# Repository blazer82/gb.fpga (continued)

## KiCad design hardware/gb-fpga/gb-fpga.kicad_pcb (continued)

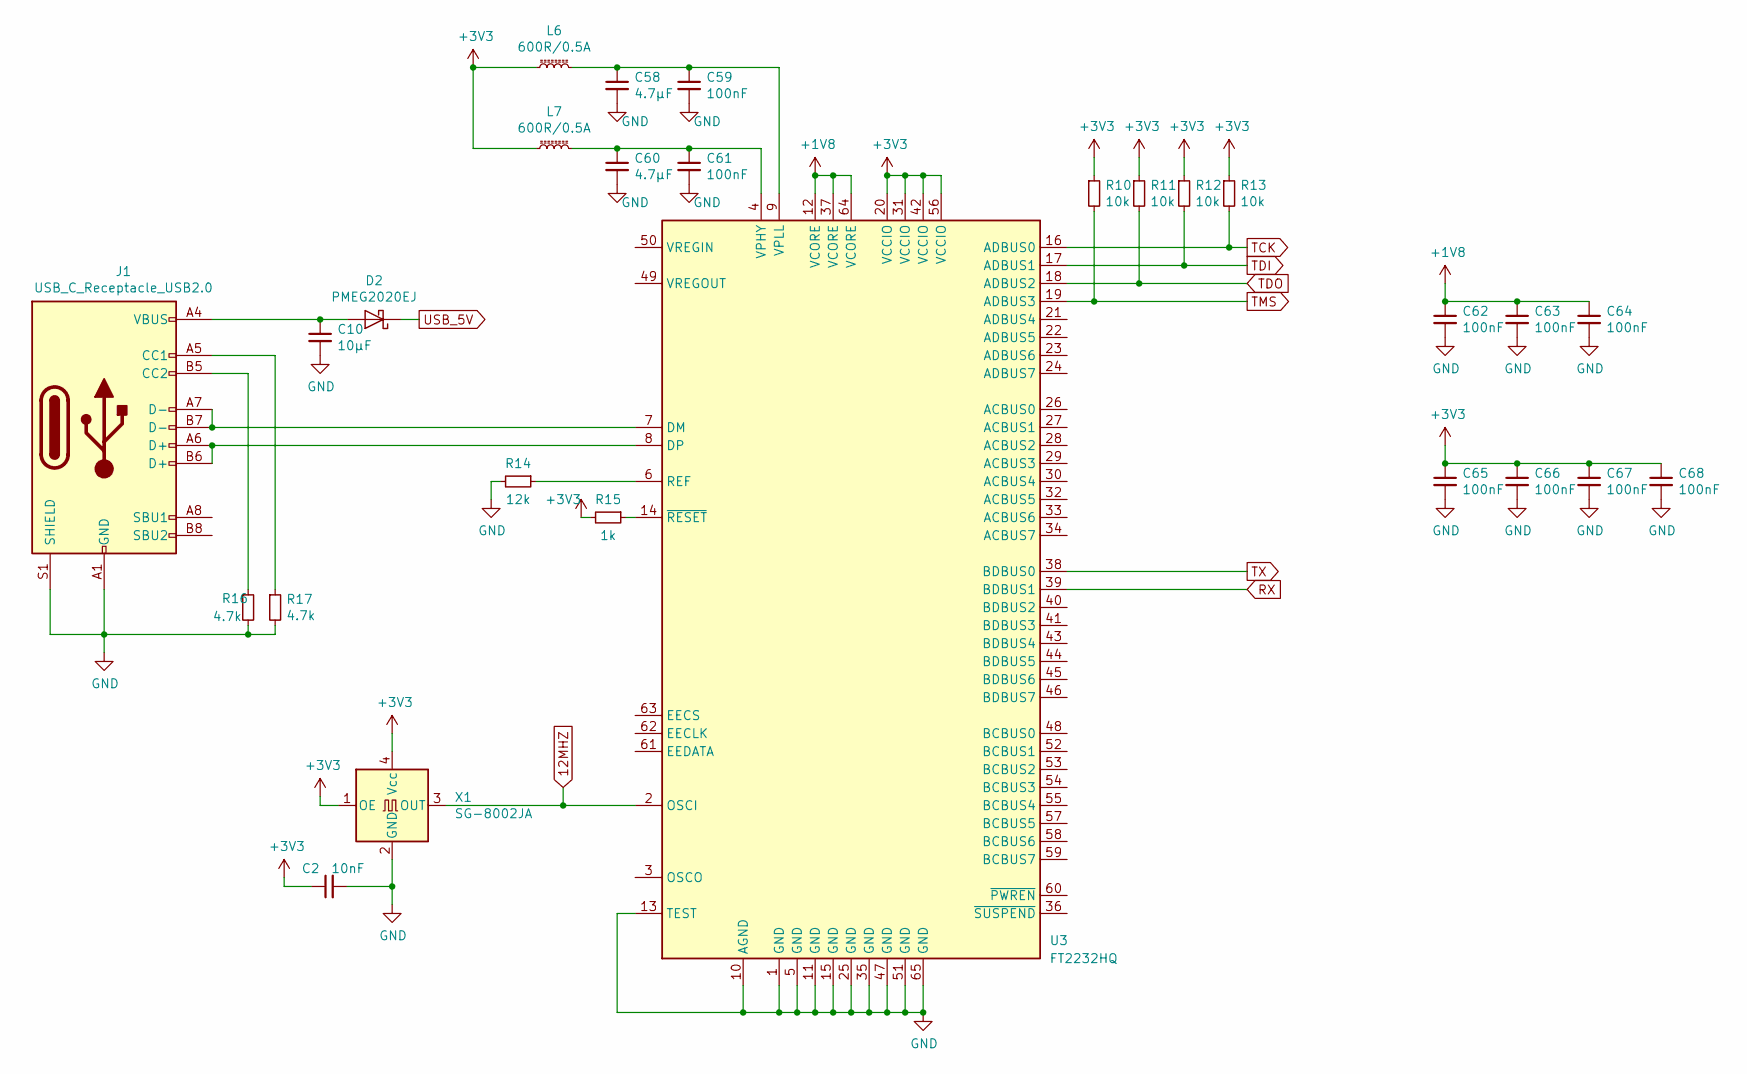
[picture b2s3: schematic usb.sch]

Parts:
C2: 10nF; C_0402_1005Metric; Manufacturer Part Number CL05B103KB5NNNC
C10: 10µF; C_0402_1005Metric; Manufacturer Part Number CL05A106MP5NUNC
C58, C60: 4.7µF; C_0402_1005Metric; Manufacturer Part Number CL05A475KP5NRNC
C59, C61, C62, C63, C64, C65, C66, C67, C68: 100nF; C_0402_1005Metric; Manufacturer Part Number CL05B104KO5NNNC
D2: PMEG2020EJ; D_SOD-323F; Manufacturer Part Number PMEG2020EJF
J1: USB_C_Receptacle_USB2.0; USB_C_Receptacle_XKB_U262-16XN-4BVC11; Manufacturer Part Number U262-161N-4BVC11
L6, L7: 600R/0.5A; L_0402_1005Metric; Manufacturer Part Number BLM15AX601SN1D
R10, R11, R12, R13: 10k; R_0402_1005Metric; Manufacturer Part Number RC0402JR-0710KL
R14: 12k; R_0402_1005Metric; Manufacturer Part Number RC0402FR-0712KL
R15: 1k; R_0402_1005Metric; Manufacturer Part Number RC0402JR-071KL
R16, R17: 4.7k; R_0402_1005Metric; Manufacturer Part Number RC0402JR-074K7L
U3: FT2232HQ; QFN-64-1EP_9x9mm_P0.5mm_EP4.35x4.35mm; Manufacturer Part Number FT2232HQ-REEL
X1: SG-8002JA; Oscillator_SMD_Abracon_ASE-4Pin_3.2x2.5mm; Manufacturer Part Number CB3LV-3C-12M000000

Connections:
12MHZ: U3.2 (OSCI), X1.3 (OUT); also elsewhere on the board
+1V8: C62.1, C63.1, C64.1, U3.12 (VCORE), U3.37 (VCORE), U3.64 (VCORE); also elsewhere on the board
+3V3: C2.1, C65.1, C66.1, C67.1, C68.1, L6.1, L7.1, R10.1, R11.1, R12.1, R13.1, R15.2, U3.20 (VCCIO), U3.31 (VCCIO), U3.42 (VCCIO), U3.56 (VCCIO), X1.1 (OE), X1.4 (Vcc); also elsewhere on the board
GND: C2.2, C10.2, C58.2, C59.2, C60.2, C61.2, C62.2, C63.2, C64.2, C65.2, C66.2, C67.2, C68.2, J1.A1 (GND), J1.A12 (GND), J1.B1 (GND), J1.B12 (GND), J1.S1 (SHIELD), R14.2, R16.2, R17.2, U3.1 (GND), U3.5 (GND), U3.10 (AGND), U3.11 (GND), U3.13 (TEST), U3.15 (GND), U3.25 (GND), U3.35 (GND), U3.47 (GND), U3.51 (GND), U3.65 (GND), X1.2 (GND); also elsewhere on the board
unnamed: C10.1, D2.2 (A), J1.A4 (VBUS), J1.A9 (VBUS), J1.B4 (VBUS), J1.B9 (VBUS)
unnamed: C58.1, C59.1, L6.2, U3.9 (VPLL)
unnamed: C60.1, C61.1, L7.2, U3.4 (VPHY)
unnamed: J1.A5 (CC1), R17.1
unnamed: J1.A6 (D+), J1.B6 (D+), U3.8 (DP)
unnamed: J1.A7 (D-), J1.B7 (D-), U3.7 (DM)
unnamed: J1.B5 (CC2), R16.1
unnamed: R14.1, U3.6 (REF)
unnamed: R15.1, U3.14 (~RESET)
RX: U3.39 (BDBUS1); also elsewhere on the board
TCK: R13.2, U3.16 (ADBUS0); also elsewhere on the board
TDI: R12.2, U3.17 (ADBUS1); also elsewhere on the board
TDO: R11.2, U3.18 (ADBUS2); also elsewhere on the board
TMS: R10.2, U3.19 (ADBUS3); also elsewhere on the board
TX: U3.38 (BDBUS0); also elsewhere on the board

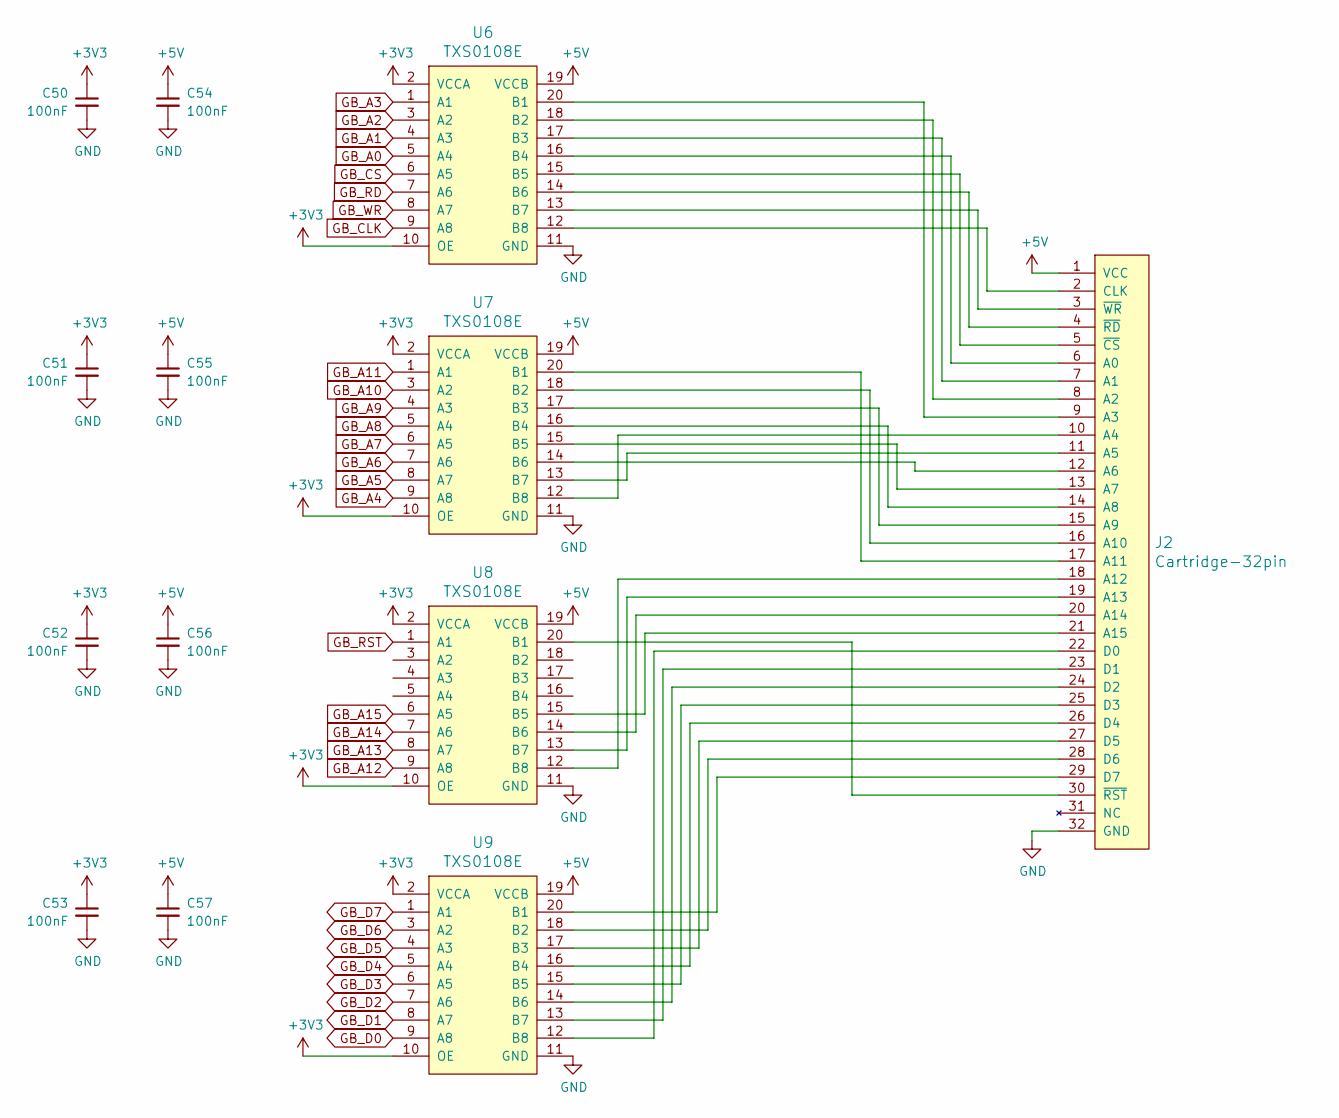
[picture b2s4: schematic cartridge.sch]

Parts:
C50, C51, C52, C53, C54, C55, C56, C57: 100nF; C_0402_1005Metric
J2: Cartridge-32pin; Cartridge-DMG
U6, U7, U8, U9: TXS0108E; TSSOP-20_4.4x6.5mm_P0.65mm

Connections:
+3V3: C50.1, C51.1, C52.1, C53.1, U6.2 (VCCA), U6.10 (OE), U7.2 (VCCA), U7.10 (OE), U8.2 (VCCA), U8.10 (OE), U9.2 (VCCA), U9.10 (OE); also elsewhere on the board
+5V: C54.1, C55.1, C56.1, C57.1, J2.1 (VCC), U6.19 (VCCB), U7.19 (VCCB), U8.19 (VCCB), U9.19 (VCCB); also elsewhere on the board
GB_A0: U6.5 (A4); also elsewhere on the board
GB_A1: U6.4 (A3); also elsewhere on the board
GB_A2: U6.3 (A2); also elsewhere on the board
GB_A3: U6.1 (A1); also elsewhere on the board
GB_A4: U7.9 (A8); also elsewhere on the board
GB_A5: U7.8 (A7); also elsewhere on the board
GB_A6: U7.7 (A6); also elsewhere on the board
GB_A7: U7.6 (A5); also elsewhere on the board
GB_A8: U7.5 (A4); also elsewhere on the board
GB_A9: U7.4 (A3); also elsewhere on the board
GB_A10: U7.3 (A2); also elsewhere on the board
GB_A11: U7.1 (A1); also elsewhere on the board
GB_A12: U8.9 (A8); also elsewhere on the board
GB_A13: U8.8 (A7); also elsewhere on the board
GB_A14: U8.7 (A6); also elsewhere on the board
GB_A15: U8.6 (A5); also elsewhere on the board
GB_CLK: U6.9 (A8); also elsewhere on the board
GB_CS: U6.6 (A5); also elsewhere on the board
GB_D0: U9.9 (A8); also elsewhere on the board
GB_D1: U9.8 (A7); also elsewhere on the board
GB_D2: U9.7 (A6); also elsewhere on the board
GB_D3: U9.6 (A5); also elsewhere on the board
GB_D4: U9.5 (A4); also elsewhere on the board
GB_D5: U9.4 (A3); also elsewhere on the board
GB_D6: U9.3 (A2); also elsewhere on the board
GB_D7: U9.1 (A1); also elsewhere on the board
GB_RD: U6.7 (A6); also elsewhere on the board
GB_RST: U8.1 (A1); also elsewhere on the board
GB_WR: U6.8 (A7); also elsewhere on the board
GND: C50.2, C51.2, C52.2, C53.2, C54.2, C55.2, C56.2, C57.2, J2.32 (GND), U6.11 (GND), U7.11 (GND), U8.11 (GND), U9.11 (GND); also elsewhere on the board
unnamed: J2.2 (CLK), U6.12 (B8)
unnamed: J2.3 (~WR~), U6.13 (B7)
unnamed: J2.4 (~RD~), U6.14 (B6)
unnamed: J2.5 (~CS~), U6.15 (B5)
unnamed: J2.6 (A0), U6.16 (B4)
unnamed: J2.7 (A1), U6.17 (B3)
unnamed: J2.8 (A2), U6.18 (B2)
unnamed: J2.9 (A3), U6.20 (B1)
unnamed: J2.10 (A4), U7.12 (B8)
unnamed: J2.11 (A5), U7.13 (B7)
unnamed: J2.12 (A6), U7.14 (B6)
unnamed: J2.13 (A7), U7.15 (B5)
unnamed: J2.14 (A8), U7.16 (B4)
unnamed: J2.15 (A9), U7.17 (B3)
unnamed: J2.16 (A10), U7.18 (B2)
unnamed: J2.17 (A11), U7.20 (B1)
unnamed: J2.18 (A12), U8.12 (B8)
unnamed: J2.19 (A13), U8.13 (B7)
unnamed: J2.20 (A14), U8.14 (B6)
unnamed: J2.21 (A15), U8.15 (B5)
unnamed: J2.22 (D0), U9.12 (B8)
unnamed: J2.23 (D1), U9.13 (B7)
unnamed: J2.24 (D2), U9.14 (B6)
unnamed: J2.25 (D3), U9.15 (B5)
unnamed: J2.26 (D4), U9.16 (B4)
unnamed: J2.27 (D5), U9.17 (B3)
unnamed: J2.28 (D6), U9.18 (B2)
unnamed: J2.29 (D7), U9.20 (B1)
unnamed: J2.30 (~RST~), U8.20 (B1)

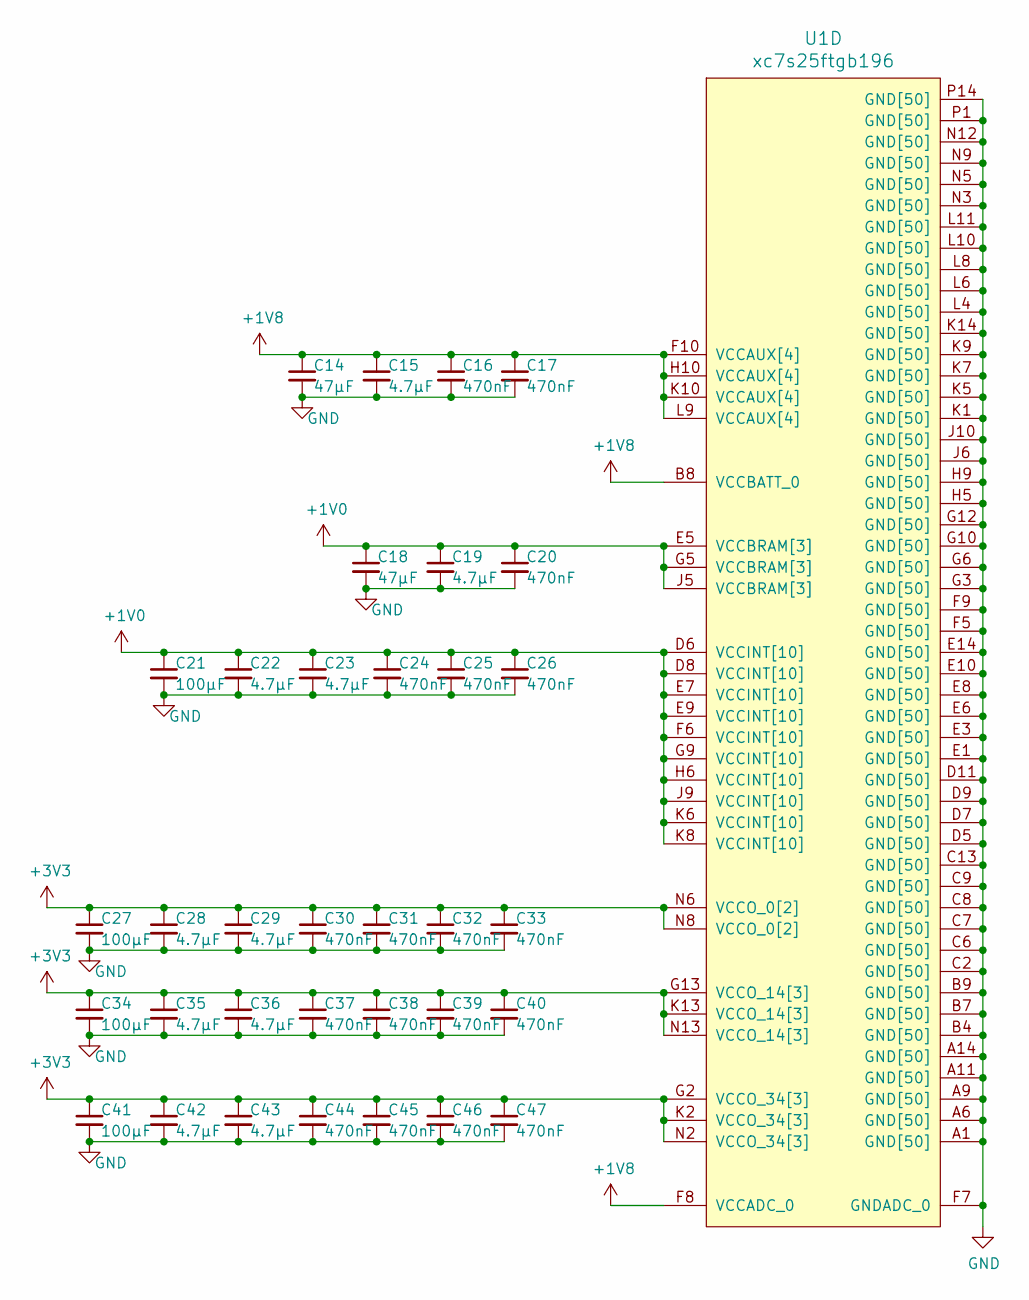
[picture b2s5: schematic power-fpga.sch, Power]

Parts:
C14, C18: 47µF; C_0201_0603Metric
C15, C19, C22, C23, C28, C29, C35, C36, C42, C43: 4.7µF; C_0201_0603Metric; Manufacturer Part Number GRM035R60J475ME15D
C16, C17, C20, C24, C25, C26, C30, C31, C32, C33, C37, C38, C39, C40, C44, C45, C46, C47: 470nF; C_0201_0603Metric; Manufacturer Part Number GRM033R60J474KE90D
C21, C27, C34, C41: 100µF; C_0201_0603Metric
U1: xc7s25ftgb196; Xilinx_FTGB196; Manufacturer Part Number XC7S25-1FTGB196C

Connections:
+1V0: C18.1, C19.1, C20.1, C21.1, C22.1, C23.1, C24.1, C25.1, C26.1, U1.D6 (VCCINT[10]), U1.D8 (VCCINT[10]), U1.E5 (VCCBRAM[3]), U1.E7 (VCCINT[10]), U1.E9 (VCCINT[10]), U1.F6 (VCCINT[10]), U1.G5 (VCCBRAM[3]), U1.G9 (VCCINT[10]), U1.H6 (VCCINT[10]), U1.J5 (VCCBRAM[3]), U1.J9 (VCCINT[10]), U1.K6 (VCCINT[10]), U1.K8 (VCCINT[10]); also elsewhere on the board
+1V8: C14.1, C15.1, C16.1, C17.1, U1.B8 (VCCBATT_0), U1.F8 (VCCADC_0), U1.F10 (VCCAUX[4]), U1.H10 (VCCAUX[4]), U1.K10 (VCCAUX[4]), U1.L9 (VCCAUX[4]); also elsewhere on the board
+3V3: C27.1, C28.1, C29.1, C30.1, C31.1, C32.1, C33.1, C34.1, C35.1, C36.1, C37.1, C38.1, C39.1, C40.1, C41.1, C42.1, C43.1, C44.1, C45.1, C46.1, C47.1, U1.G2 (VCCO_34[3]), U1.G13 (VCCO_14[3]), U1.K2 (VCCO_34[3]), U1.K13 (VCCO_14[3]), U1.N2 (VCCO_34[3]), U1.N6 (VCCO_0[2]), U1.N8 (VCCO_0[2]), U1.N13 (VCCO_14[3]); also elsewhere on the board
GND: C14.2, C15.2, C16.2, C17.2, C18.2, C19.2, C20.2, C21.2, C22.2, C23.2, C24.2, C25.2, C26.2, C27.2, C28.2, C29.2, C30.2, C31.2, C32.2, C33.2, C34.2, C35.2, C36.2, C37.2, C38.2, C39.2, C40.2, C41.2, C42.2, C43.2, C44.2, C45.2, C46.2, C47.2, U1.A1 (GND[50]), U1.A6 (GND[50]), U1.A9 (GND[50]), U1.A11 (GND[50]), U1.A14 (GND[50]), U1.B4 (GND[50]), U1.B7 (GND[50]), U1.B9 (GND[50]), U1.C2 (GND[50]), U1.C6 (GND[50]), U1.C7 (GND[50]), U1.C8 (GND[50]), U1.C9 (GND[50]), U1.C13 (GND[50]), U1.D5 (GND[50]), U1.D7 (GND[50]), U1.D9 (GND[50]), U1.D11 (GND[50]), U1.E1 (GND[50]), U1.E3 (GND[50]), U1.E6 (GND[50]), U1.E8 (GND[50]), U1.E10 (GND[50]), U1.E14 (GND[50]), U1.F5 (GND[50]), U1.F7 (GNDADC_0), U1.F9 (GND[50]), U1.G3 (GND[50]), U1.G6 (GND[50]), U1.G10 (GND[50]), U1.G12 (GND[50]), U1.H5 (GND[50]), U1.H9 (GND[50]), U1.J6 (GND[50]), U1.J10 (GND[50]), U1.K1 (GND[50]), U1.K5 (GND[50]), U1.K7 (GND[50]), U1.K9 (GND[50]), U1.K14 (GND[50]), U1.L4 (GND[50]), U1.L6 (GND[50]), U1.L8 (GND[50]), U1.L10 (GND[50]), U1.L11 (GND[50]), U1.N3 (GND[50]), U1.N5 (GND[50]), U1.N9 (GND[50]), U1.N12 (GND[50]), U1.P1 (GND[50]), U1.P14 (GND[50]); also elsewhere on the board

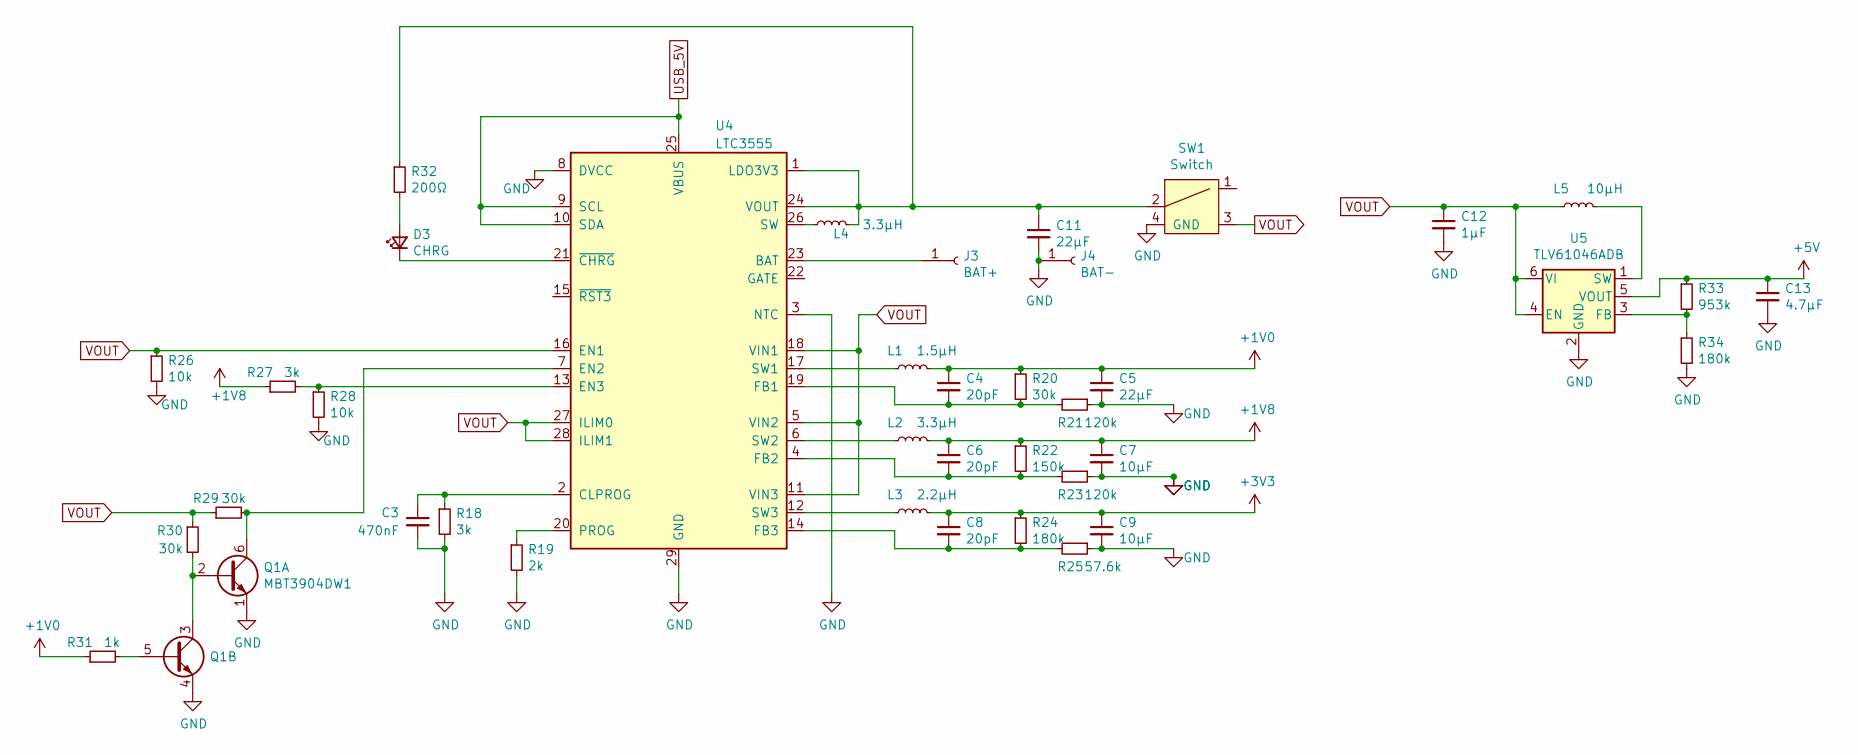
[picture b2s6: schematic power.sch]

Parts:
C3: 470nF; C_0402_1005Metric; Manufacturer Part Number CL05A474KP5NNNC
C4, C6, C8: 20pF; C_0402_1005Metric; Manufacturer Part Number CL05C220JB5NNNC
C5, C11: 22µF; C_0402_1005Metric; Manufacturer Part Number GRM155R60J226ME11D
C7, C9: 10µF; C_0402_1005Metric; Manufacturer Part Number CL05A106MP5NUNC
C12: 1µF; C_0402_1005Metric; Manufacturer Part Number CL05A105KO5NNNC
C13: 4.7µF; C_0402_1005Metric; Manufacturer Part Number CL05A475KP5NRNC
D3: CHRG; LED_0402_1005Metric; Manufacturer Part Number NCD0402B1
J3: BAT+; PinHeader_1x01_P2.54mm_Vertical
J4: BAT-; PinHeader_1x01_P2.54mm_Vertical
L1: 1.5µH; L_0402_1005Metric; Manufacturer Part Number SDFL1005Q1R5KTF
L2, L4: 3.3µH; L_0402_1005Metric; Manufacturer Part Number SDFL1005Q3R3KTF
L3: 2.2µH; L_0402_1005Metric; Manufacturer Part Number SDFL1005Q2R2KTF
L5: 10µH; L_0603_1608Metric; Manufacturer Part Number SDFL1608S100KTF
Q1: MBT3904DW1; SOT-363_SC-70-6; Manufacturer Part Number MBT3904DW1T1H
R18, R27: 3k; R_0402_1005Metric; Manufacturer Part Number RC0402FR-073KL
R19: 2k; R_0402_1005Metric; Manufacturer Part Number RC0402FR-072KL
R20, R29, R30: 30k; R_0402_1005Metric; Manufacturer Part Number AF0402FR-0730KL
R21, R23: 120k; R_0402_1005Metric; Manufacturer Part Number RC0402FR-07120KL
R22: 150k; R_0402_1005Metric; Manufacturer Part Number RC0402FR-07150KL
R24, R34: 180k; R_0402_1005Metric; Manufacturer Part Number RC0402FR-07180KL
R25: 57.6k; R_0402_1005Metric; Manufacturer Part Number RC0402FR-0757K6L
R26, R28: 10k; R_0402_1005Metric; Manufacturer Part Number RC0402JR-0710KL
R31: 1k; R_0402_1005Metric; Manufacturer Part Number RC0402JR-071KL
R32: 200Ω; R_0402_1005Metric; Manufacturer Part Number AC0402JR-07200RL
R33: 953k; R_0402_1005Metric; Manufacturer Part Number RC0402FR-07953KL
SW1: Switch; EG2215; Manufacturer Part Number EG2215
U4: LTC3555; QFN-28-1EP_4x5mm_P0.5mm_EP2.65x3.65mm; Manufacturer Part Number LTC3555IUFD-1#PBF
U5: TLV61046ADB; SOT-23-6; Manufacturer Part Number TLV61046ADBVR

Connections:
+1V0: C4.1, C5.1, L1.2, R20.1, R31.1; also elsewhere on the board
+1V8: C6.1, C7.1, L2.2, R22.1, R27.1; also elsewhere on the board
+3V3: C8.1, C9.1, L3.2, R24.1; also elsewhere on the board
+5V: C13.1, R33.1, U5.5 (VOUT); also elsewhere on the board
GND: C3.2, C5.2, C7.2, C9.2, C11.2, C12.2, C13.2, J4.1, Q1.1 (E1), Q1.4 (E2), R18.2, R19.2, R21.1, R23.1, R25.1, R26.2, R28.2, R34.2, SW1.4 (GND), U4.3 (NTC), U4.8 (DVCC), U4.29 (GND), U5.2 (GND); also elsewhere on the board
unnamed: C3.1, R18.1, U4.2 (CLPROG)
unnamed: C4.2, R20.2, R21.2, U4.19 (FB1)
unnamed: C6.2, R22.2, R23.2, U4.4 (FB2)
unnamed: C8.2, R24.2, R25.2, U4.14 (FB3)
unnamed: C11.1, L4.2, R32.1, SW1.2, U4.1 (LDO3V3), U4.24 (VOUT)
unnamed: D3.1 (K), U4.21 (~CHRG)
unnamed: D3.2 (A), R32.2
unnamed: J3.1, U4.23 (BAT)
unnamed: L1.1, U4.17 (SW1)
unnamed: L2.1, U4.6 (SW2)
unnamed: L3.1, U4.12 (SW3)
unnamed: L4.1, U4.26 (SW)
unnamed: L5.2, U5.1 (SW)
unnamed: Q1.2 (B1), Q1.3 (C2), R30.2
unnamed: Q1.5 (B2), R31.2
unnamed: Q1.6 (C1), R29.2, U4.7 (EN2)
unnamed: R19.1, U4.20 (PROG)
unnamed: R27.2, R28.1, U4.13 (EN3)
unnamed: R33.2, R34.1, U5.3 (FB)

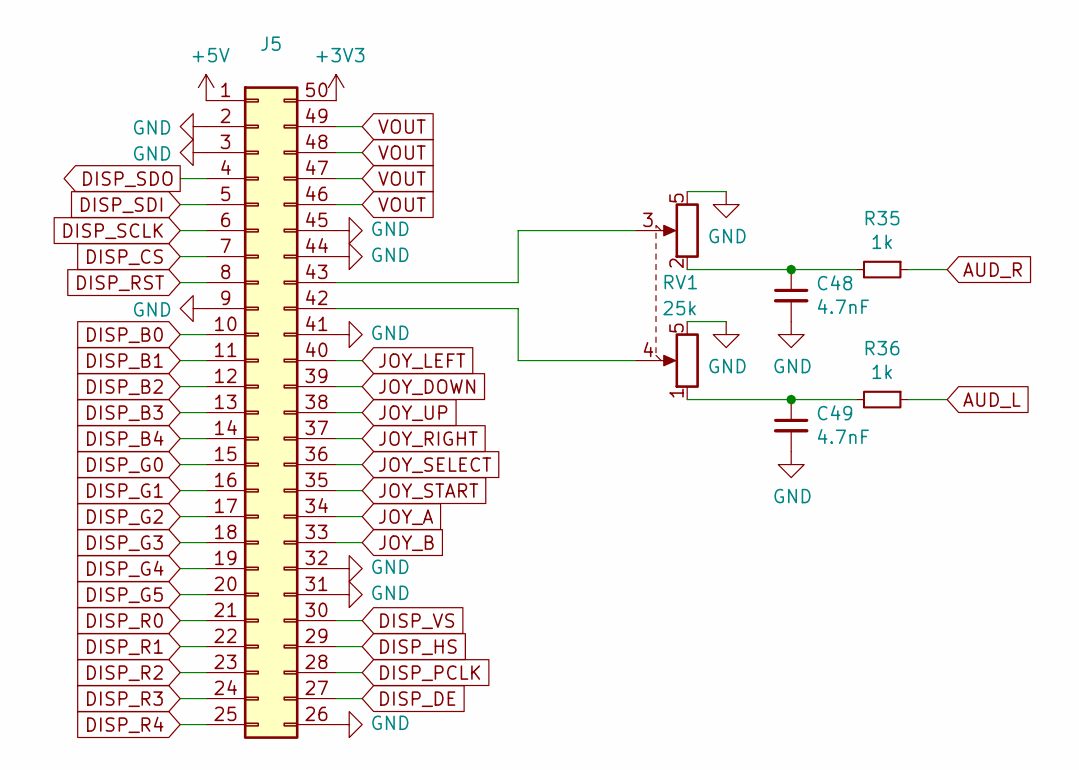
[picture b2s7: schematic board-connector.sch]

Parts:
C48, C49: 4.7nF; C_0402_1005Metric
J5: Conn_02x25_Counter_Clockwise; Hirose_FH12-50S-0.5SH_1x50-1MP_P0.50mm_Horizontal
R35, R36: 1k; R_0402_1005Metric
RV1: 25k; Dual_Pot

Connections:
+3V3: J5.50; also elsewhere on the board
+5V: J5.1; also elsewhere on the board
AUD_L: R36.1; also elsewhere on the board
AUD_R: R35.1; also elsewhere on the board
DISP_B0: J5.10; also elsewhere on the board
DISP_B1: J5.11; also elsewhere on the board
DISP_B2: J5.12; also elsewhere on the board
DISP_B3: J5.13; also elsewhere on the board
DISP_B4: J5.14; also elsewhere on the board
DISP_CS: J5.7; also elsewhere on the board
DISP_DE: J5.27; also elsewhere on the board
DISP_G0: J5.15; also elsewhere on the board
DISP_G1: J5.16; also elsewhere on the board
DISP_G2: J5.17; also elsewhere on the board
DISP_G3: J5.18; also elsewhere on the board
DISP_G4: J5.19; also elsewhere on the board
DISP_G5: J5.20; also elsewhere on the board
DISP_HS: J5.29; also elsewhere on the board
DISP_PCLK: J5.28; also elsewhere on the board
DISP_R0: J5.21; also elsewhere on the board
DISP_R1: J5.22; also elsewhere on the board
DISP_R2: J5.23; also elsewhere on the board
DISP_R3: J5.24; also elsewhere on the board
DISP_R4: J5.25; also elsewhere on the board
DISP_RST: J5.8; also elsewhere on the board
DISP_SCLK: J5.6; also elsewhere on the board
DISP_SDI: J5.5; also elsewhere on the board
DISP_SDO: J5.4; also elsewhere on the board
DISP_VS: J5.30; also elsewhere on the board
GND: C48.2, C49.2, J5.2, J5.3, J5.9, J5.26, J5.31, J5.32, J5.41, J5.44, J5.45, RV1.5; also elsewhere on the board
JOY_A: J5.34; also elsewhere on the board
JOY_B: J5.33; also elsewhere on the board
JOY_DOWN: J5.39; also elsewhere on the board
JOY_LEFT: J5.40; also elsewhere on the board
JOY_RIGHT: J5.37; also elsewhere on the board
JOY_SELECT: J5.36; also elsewhere on the board
JOY_START: J5.35; also elsewhere on the board
JOY_UP: J5.38; also elsewhere on the board
unnamed: C48.1, R35.2, RV1.2
unnamed: C49.1, R36.2, RV1.1
unnamed: J5.42, RV1.4
unnamed: J5.43, RV1.3

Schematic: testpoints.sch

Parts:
TP1: 1V0; TestPoint_Pad_1.0x1.0mm
TP2: 1V8; TestPoint_THTPad_1.0x1.0mm_Drill0.5mm
TP3: 3V3; TestPoint_THTPad_1.0x1.0mm_Drill0.5mm
TP4: 5V; TestPoint_THTPad_1.0x1.0mm_Drill0.5mm
TP5: USB5V; TestPoint_Pad_1.0x1.0mm
TP6: VOUT; TestPoint_THTPad_1.0x1.0mm_Drill0.5mm
TP7, TP8: GND; TestPoint_THTPad_1.5x1.5mm_Drill0.7mm
TP9: AUD_L; TestPoint_Pad_D1.0mm
TP10: AUD_R; TestPoint_Pad_D1.0mm
TP11: 12MHZ; TestPoint_Pad_D1.0mm
TP12: TCK; TestPoint_Pad_D1.0mm
TP13: SCLK; TestPoint_Pad_D1.0mm

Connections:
12MHZ: TP11.1; also elsewhere on the board
+1V0: TP1.1; also elsewhere on the board
+1V8: TP2.1; also elsewhere on the board
+3V3: TP3.1; also elsewhere on the board
+5V: TP4.1; also elsewhere on the board
AUD_L: TP9.1; also elsewhere on the board
AUD_R: TP10.1; also elsewhere on the board
GND: TP7.1, TP8.1; also elsewhere on the board
SCLK: TP13.1; also elsewhere on the board
TCK: TP12.1; also elsewhere on the board

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
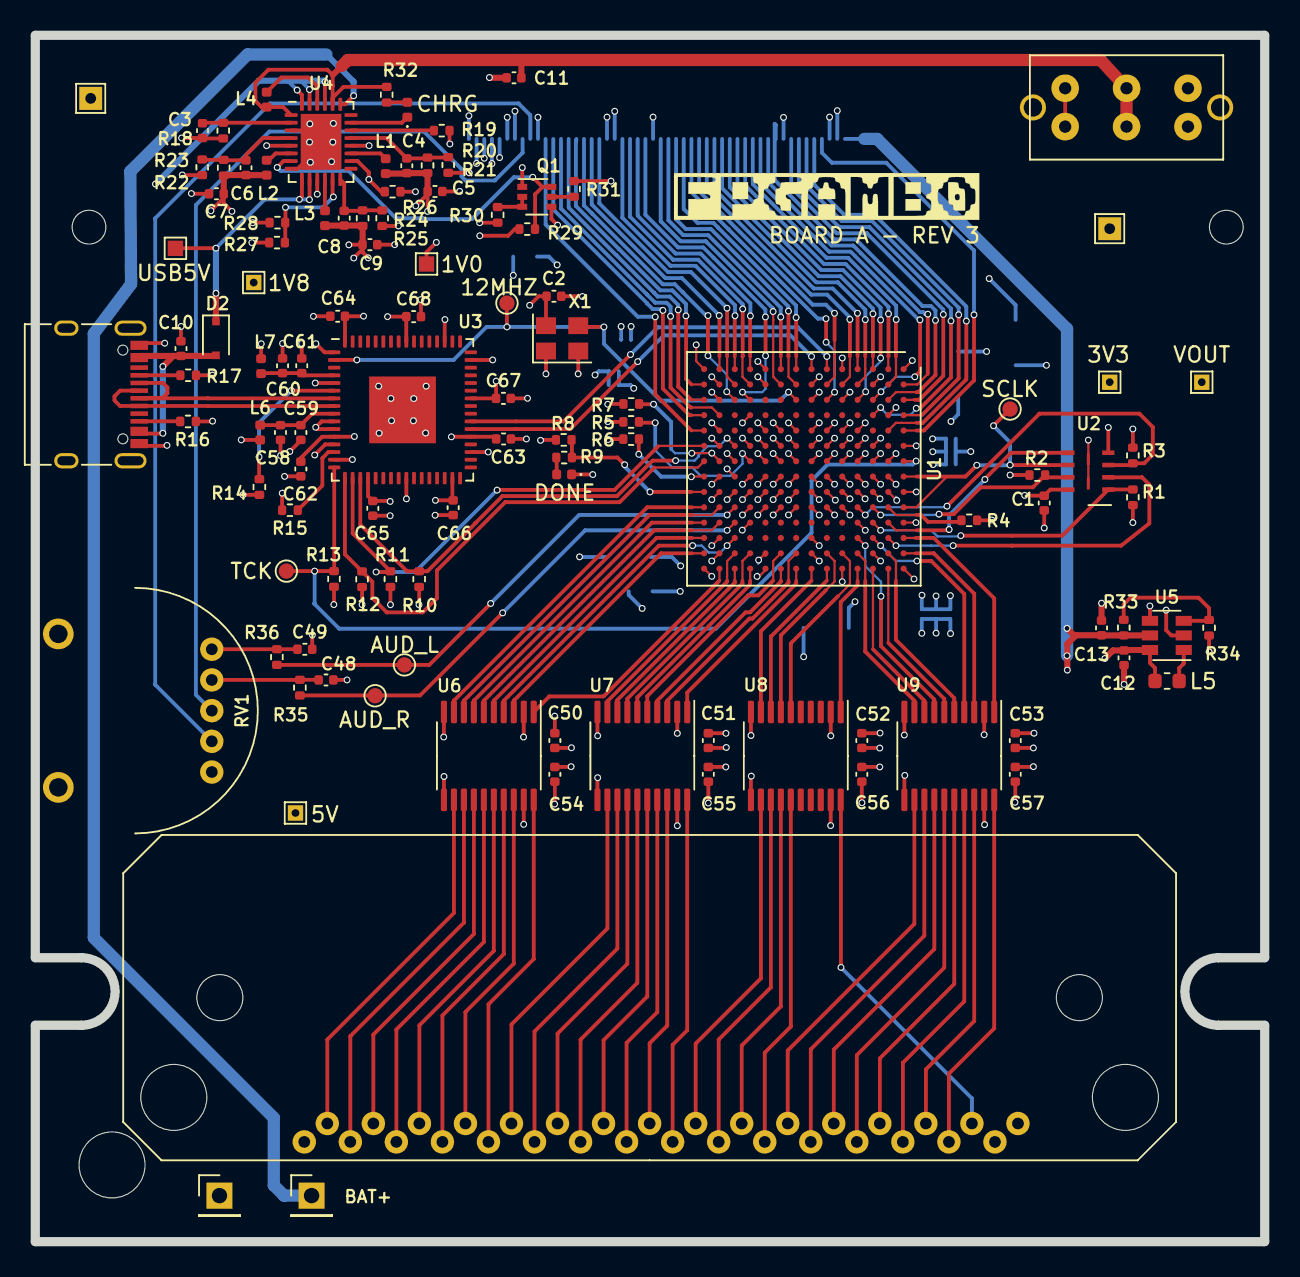
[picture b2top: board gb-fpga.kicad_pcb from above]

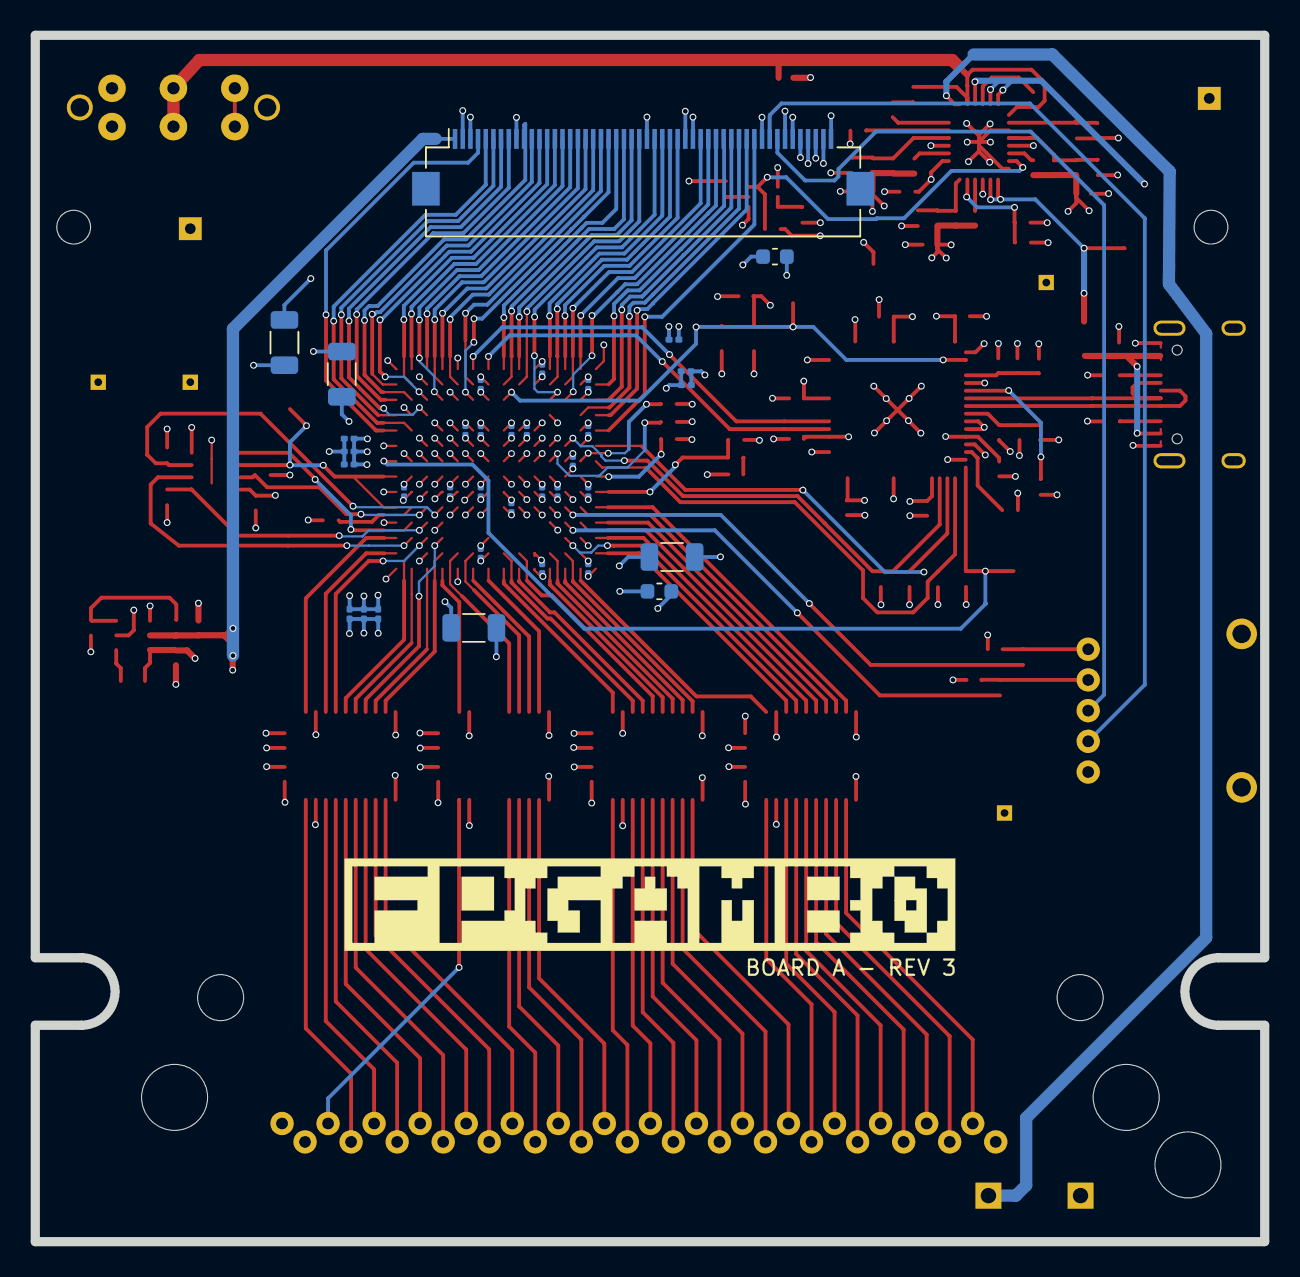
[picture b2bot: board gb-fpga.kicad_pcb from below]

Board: 4 copper layers, 80.1 x 78.6 mm, 145 parts (35 on the bottom side), 151 nets.

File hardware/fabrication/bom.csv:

Designator;Value;Package/Footprint;Mfg Part #;Qty
C1, C50, C51, C52, C53, C54, C55, C56, C57, C59, C61, C62, C63, C64, C65, C66, C67, C68;100nF;0402;CL05B104KO5NNNC;18
C1;100nF;0402;CL05B104KO5NNNC;1
C50;100nF;0402;CL05B104KO5NNNC;1
C51;100nF;0402;CL05B104KO5NNNC;1
C52;100nF;0402;CL05B104KO5NNNC;1
C53;100nF;0402;CL05B104KO5NNNC;1
C54;100nF;0402;CL05B104KO5NNNC;1
C55;100nF;0402;CL05B104KO5NNNC;1
C56;100nF;0402;CL05B104KO5NNNC;1
C57;100nF;0402;CL05B104KO5NNNC;1
C59;100nF;0402;CL05B104KO5NNNC;1
C61;100nF;0402;CL05B104KO5NNNC;1
C62;100nF;0402;CL05B104KO5NNNC;1
C63;100nF;0402;CL05B104KO5NNNC;1
C64;100nF;0402;CL05B104KO5NNNC;1
C65;100nF;0402;CL05B104KO5NNNC;1
C66;100nF;0402;CL05B104KO5NNNC;1
C67;100nF;0402;CL05B104KO5NNNC;1
C68;100nF;0402;CL05B104KO5NNNC;1
C2;10nF;0402;CL05B103KB5NNNC;1
C3;470nF;0402;CL05A474KP5NNNC;1
C4, C6, C8;20pF;0402;CL05C220JB5NNNC;3
C5, C11;22µF;0402;GRM155R60J226ME11D;2
C7, C9, C10;10µF;0402;CL05A106MP5NUNC;3
C12;1µF;0402;CL05A105KO5NNNC;1
C14, C18;47µF;0603;CL10A476MQ8QRNC;2
C21, C27, C34, C41;100µF;1206;GRM31CR61A107ME05L;4
C15, C19, C22, C23, C28, C29, C35, C36, C42, C43;4.7µF;0201;GRM035R60J475ME15D;10
C16, C17, C20, C24, C25, C26, C30, C31, C32, C33, C37, C38, C39, C40, C44, C45, C46, C47;470nF;0201;GRM033R60J474KE90D;18
C48, C49;4.7nF;0402;CL05B472KA5NNNC;2
C13, C58, C60;4.7µF;0402;CL05A475KP5NRNC;3
D1;DONE;0402;NCD0402G1;1
D2;PMEG2020EJ;SOD-323;PMEG2020EJF;1
D3;CHRG;0402;NCD0402B1;1
J1;USB_C_Receptacle_USB2.0;;U262-161N-4BVC11;1
J5;Conn_02x25_Counter_Clockwise;;FH12-50S-0.5SH(55);1
L1;1.5µH;0402;SDFL1005Q1R5KTF;1
L2, L4;3.3µH;0402;SDFL1005Q3R3KTF;2
L3;2.2µH;0402;SDFL1005Q2R2KTF;1
L5;10µH;0603;SDFL1608S100KTF;1
L6, L7;600R/0.5A;0402;BLM15AX601SN1D;2
Q1;MBT3904DW1;SOT-363;MBT3904DW1T1H;1
R1, R5, R6, R7, R16, R17;4.7k;0402;RC0402JR-074K7L;6
R2, R3;1.8k;0402;RC0402JR-071K8L;2
R4, R15, R31, R35, R36;1k;0402;RC0402JR-071KL;5
R8, R9, R32;200Ω;0402;AC0402JR-07200RL;3
R10, R11, R12, R13, R26, R28;10k;0402;RC0402JR-0710KL;6
R14;12k;0402;RC0402FR-0712KL;1
R18, R27;3k;0402;RC0402FR-073KL;2
R19;2k;0402;RC0402FR-072KL;1
R20, R29, R30;30k;0402;AF0402FR-0730KL;3
R21, R23;120k;0402;RC0402FR-07120KL;2
R22;150k;0402;RC0402FR-07150KL;1
R24, R34;180k;0402;RC0402FR-07180KL;2
R25;57.6k;0402;RC0402FR-0757K6L;1
R33;953k;0402;RC0402FR-07953KL;1
U1;xc7s25ftgb196;;XC7S25-1FTGB196C;1
U2;MX25R3235FZBxx1;USON-8;MX25R3235FZBIL0;1
U3;FT2232HQ;QFN-64;FT2232HQ-REEL;1
U4;LTC3555;QFN-28;LTC3555IUFD-1#PBF;1
U5;TLV61046ADB;SOT-23-6;TLV61046ADBVR;1
U6, U7, U8, U9;TXS0108E;TSSOP-20;TXS0108EPWR;4
X1;SG-8002JA;;CB3LV-3C-12M000000;1

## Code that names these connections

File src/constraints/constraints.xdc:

## 12 MHz System Clock
set_property -dict {PACKAGE_PIN H3 IOSTANDARD LVCMOS33} [get_ports clk]
create_clock -period 83.330 -name sys_clk_pin -waveform {0.000 41.660} -add [get_ports clk]

## Because system clock is not on the correct pin
set_property CLOCK_DEDICATED_ROUTE FALSE [get_nets clk_IBUF]

## USB UART
## Note: Port names are from the perspoctive of the FPGA.
set_property -dict { PACKAGE_PIN F1   IOSTANDARD LVCMOS33 } [get_ports { uart_tx }]
set_property -dict { PACKAGE_PIN G1   IOSTANDARD LVCMOS33 } [get_ports { uart_rx }]

## Cartridge ports
set_property -dict { PACKAGE_PIN P10   IOSTANDARD LVCMOS33 } [get_ports { gb_clk }]
set_property -dict { PACKAGE_PIN N10   IOSTANDARD LVCMOS33 } [get_ports { gb_wr }]
set_property -dict { PACKAGE_PIN P11   IOSTANDARD LVCMOS33 } [get_ports { gb_rd }]
set_property -dict { PACKAGE_PIN N11   IOSTANDARD LVCMOS33 } [get_ports { gb_cs }]
set_property -dict { PACKAGE_PIN P12   IOSTANDARD LVCMOS33 } [get_ports { gb_a[0] }]
set_property -dict { PACKAGE_PIN M12   IOSTANDARD LVCMOS33 } [get_ports { gb_a[1] }]
set_property -dict { PACKAGE_PIN P13   IOSTANDARD LVCMOS33 } [get_ports { gb_a[2] }]
set_property -dict { PACKAGE_PIN N14   IOSTANDARD LVCMOS33 } [get_ports { gb_a[3] }]
set_property -dict { PACKAGE_PIN M13   IOSTANDARD LVCMOS33 } [get_ports { gb_a[4] }]
set_property -dict { PACKAGE_PIN M14   IOSTANDARD LVCMOS33 } [get_ports { gb_a[5] }]
set_property -dict { PACKAGE_PIN L13   IOSTANDARD LVCMOS33 } [get_ports { gb_a[6] }]
set_property -dict { PACKAGE_PIN L14   IOSTANDARD LVCMOS33 } [get_ports { gb_a[7] }]
set_property -dict { PACKAGE_PIN J13   IOSTANDARD LVCMOS33 } [get_ports { gb_a[8] }]
set_property -dict { PACKAGE_PIN J14   IOSTANDARD LVCMOS33 } [get_ports { gb_a[9] }]
set_property -dict { PACKAGE_PIN H13   IOSTANDARD LVCMOS33 } [get_ports { gb_a[10] }]
set_property -dict { PACKAGE_PIN H14   IOSTANDARD LVCMOS33 } [get_ports { gb_a[11] }]
set_property -dict { PACKAGE_PIN G14   IOSTANDARD LVCMOS33 } [get_ports { gb_a[12] }]
set_property -dict { PACKAGE_PIN F14   IOSTANDARD LVCMOS33 } [get_ports { gb_a[13] }]
set_property -dict { PACKAGE_PIN F13   IOSTANDARD LVCMOS33 } [get_ports { gb_a[14] }]
set_property -dict { PACKAGE_PIN E13   IOSTANDARD LVCMOS33 } [get_ports { gb_a[15] }]
set_property -dict { PACKAGE_PIN D14   IOSTANDARD LVCMOS33 } [get_ports { gb_rst }]
set_property -dict { PACKAGE_PIN D13   IOSTANDARD LVCMOS33 } [get_ports { gb_d[0] }]
set_property -dict { PACKAGE_PIN C14   IOSTANDARD LVCMOS33 } [get_ports { gb_d[1] }]
set_property -dict { PACKAGE_PIN D12   IOSTANDARD LVCMOS33 } [get_ports { gb_d[2] }]
set_property -dict { PACKAGE_PIN B14   IOSTANDARD LVCMOS33 } [get_ports { gb_d[3] }]
set_property -dict { PACKAGE_PIN B13   IOSTANDARD LVCMOS33 } [get_ports { gb_d[4] }]
set_property -dict { PACKAGE_PIN C12   IOSTANDARD LVCMOS33 } [get_ports { gb_d[5] }]
set_property -dict { PACKAGE_PIN A13   IOSTANDARD LVCMOS33 } [get_ports { gb_d[6] }]
set_property -dict { PACKAGE_PIN A12   IOSTANDARD LVCMOS33 } [get_ports { gb_d[7] }]

## Board connector ports
#set_property -dict {PACKAGE_PIN A5 IOSTANDARD LVCMOS33} [get_ports disp_sdo]
set_property -dict { PACKAGE_PIN B5    IOSTANDARD LVCMOS33 } [get_ports { disp_sdi }]
set_property -dict { PACKAGE_PIN A4    IOSTANDARD LVCMOS33 } [get_ports disp_sclk]
set_property -dict { PACKAGE_PIN C4    IOSTANDARD LVCMOS33 } [get_ports disp_cs]
set_property -dict { PACKAGE_PIN A3    IOSTANDARD LVCMOS33 } [get_ports disp_rst]
set_property -dict { PACKAGE_PIN B3    IOSTANDARD LVCMOS33 } [get_ports {disp_r[4]}]
set_property -dict { PACKAGE_PIN A2    IOSTANDARD LVCMOS33 } [get_ports {disp_r[3]}]
set_property -dict { PACKAGE_PIN C3    IOSTANDARD LVCMOS33 } [get_ports {disp_r[2]}]
set_property -dict { PACKAGE_PIN B2    IOSTANDARD LVCMOS33 } [get_ports {disp_r[1]}]
set_property -dict { PACKAGE_PIN B1    IOSTANDARD LVCMOS33 } [get_ports {disp_r[0]}]
set_property -dict { PACKAGE_PIN D3    IOSTANDARD LVCMOS33 } [get_ports {disp_g[5]}]
set_property -dict { PACKAGE_PIN C1    IOSTANDARD LVCMOS33 } [get_ports {disp_g[4]}]
set_property -dict { PACKAGE_PIN D2    IOSTANDARD LVCMOS33 } [get_ports {disp_g[3]}]
set_property -dict { PACKAGE_PIN D1    IOSTANDARD LVCMOS33 } [get_ports {disp_g[2]}]
set_property -dict { PACKAGE_PIN E2    IOSTANDARD LVCMOS33 } [get_ports {disp_g[1]}]
set_property -dict { PACKAGE_PIN F2    IOSTANDARD LVCMOS33 } [get_ports {disp_g[0]}]
set_property -dict { PACKAGE_PIN F3    IOSTANDARD LVCMOS33 } [get_ports {disp_b[4]}]
set_property -dict { PACKAGE_PIN H1    IOSTANDARD LVCMOS33 } [get_ports {disp_b[3]}]
set_property -dict { PACKAGE_PIN H2    IOSTANDARD LVCMOS33 } [get_ports {disp_b[2]}]
set_property -dict { PACKAGE_PIN J1    IOSTANDARD LVCMOS33 } [get_ports {disp_b[1]}]
set_property -dict { PACKAGE_PIN J2    IOSTANDARD LVCMOS33 } [get_ports {disp_b[0]}]
set_property -dict { PACKAGE_PIN L3    IOSTANDARD LVCMOS33 } [get_ports disp_de]
set_property -dict { PACKAGE_PIN L1    IOSTANDARD LVCMOS33 } [get_ports disp_pclk]
set_property -dict { PACKAGE_PIN L2    IOSTANDARD LVCMOS33 } [get_ports disp_hs]
set_property -dict { PACKAGE_PIN M1    IOSTANDARD LVCMOS33 } [get_ports disp_vs]
set_property -dict { PACKAGE_PIN M2    IOSTANDARD LVCMOS33 } [get_ports { joy_b }]
set_property -dict { PACKAGE_PIN N1    IOSTANDARD LVCMOS33 } [get_ports { joy_a }]
set_property -dict { PACKAGE_PIN M3    IOSTANDARD LVCMOS33 } [get_ports { joy_start }]
set_property -dict { PACKAGE_PIN P2    IOSTANDARD LVCMOS33 } [get_ports { joy_select }]
set_property -dict { PACKAGE_PIN P3    IOSTANDARD LVCMOS33 } [get_ports { joy_right }]
set_property -dict { PACKAGE_PIN N4    IOSTANDARD LVCMOS33 } [get_ports { joy_up }]
set_property -dict { PACKAGE_PIN P4    IOSTANDARD LVCMOS33 } [get_ports { joy_down }]
set_property -dict { PACKAGE_PIN P5    IOSTANDARD LVCMOS33 } [get_ports { joy_left }]

## Audio
set_property -dict {PACKAGE_PIN M10 IOSTANDARD LVCMOS33} [get_ports audio_l]
set_property -dict {PACKAGE_PIN M11 IOSTANDARD LVCMOS33} [get_ports audio_r]

## Quad SPI Flash
## Note: QSPI clock can only be accessed through the STARTUPE2 primitive
set_property -dict { PACKAGE_PIN C11   IOSTANDARD LVCMOS33 } [get_ports { qspi_cs }]
set_property -dict { PACKAGE_PIN B11   IOSTANDARD LVCMOS33 } [get_ports { qspi_dq[0] }]
set_property -dict { PACKAGE_PIN B12   IOSTANDARD LVCMOS33 } [get_ports { qspi_dq[1] }]
#set_property -dict { PACKAGE_PIN D10   IOSTANDARD LVCMOS33 } [get_ports { qspi_dq[2] }]
#set_property -dict { PACKAGE_PIN C10   IOSTANDARD LVCMOS33 } [get_ports { qspi_dq[3] }]

set_property BITSTREAM.GENERAL.COMPRESS TRUE [current_design]
set_property BITSTREAM.CONFIG.CONFIGRATE 33 [current_design]
set_property CONFIG_MODE SPIx4 [current_design]
set_property CONFIG_VOLTAGE 3.3 [current_design]
set_property CFGBVS VCCO [current_design]

set_property BITSTREAM.CONFIG.SPI_BUSWIDTH 4 [current_design]
